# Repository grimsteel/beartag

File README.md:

# beartag

A low cost, open source BLE device tracker.

Compatible with [macless-haystack](https://github.com/dchristl/macless-haystack)

## PCB

The board is based on a WCH CH571 MCU. (Low cost BLE mcu)

It can be powered off of a single CR2032 battery, which should last at least a couple months (and potentially as long as a year)

The board includes one customizable button as well as a status LED.

## Firmware

Firmware is coming soon

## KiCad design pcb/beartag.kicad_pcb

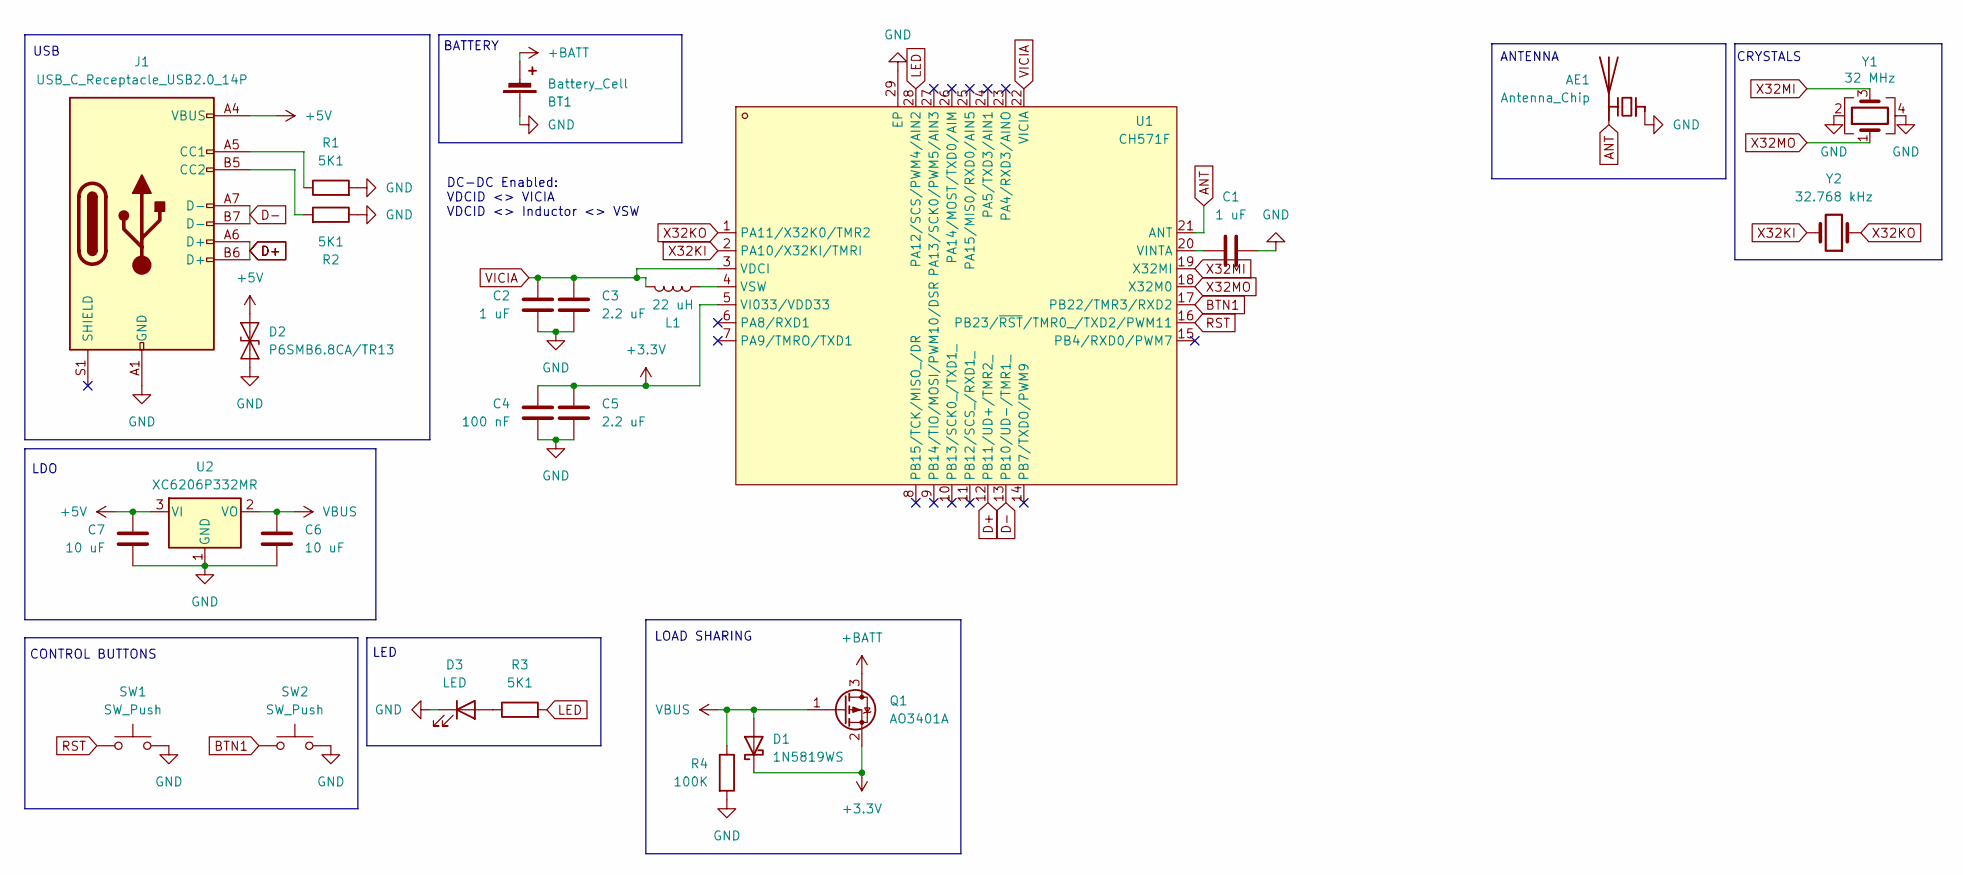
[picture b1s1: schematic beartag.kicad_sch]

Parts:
AE1: Antenna_Chip; Texas_SWRA117D_2.4GHz_Right
BT1: Battery_Cell; JST_PH_B2B-PH-K_1x02_P2.00mm_Vertical
C1, C2: 1 uF; C_0402_1005Metric; LCSC C52923
C3, C5: 2.2 uF; C_0402_1005Metric; LCSC C12530
C4: 100 nF; C_0402_1005Metric; LCSC C1525
C6, C7: 10 uF; C_0603_1608Metric; LCSC C19702
D1: 1N5819WS; D_SOD-323; LCSC C191023
D2: P6SMB6.8CA/TR13; D_SMB; LCSC C78395
D3: LED; LED_0603_1608Metric; LCSC C2286
J1: USB_C_Receptacle_USB2.0_14P; USB_C_Receptacle_HCTL_HC-TYPE-C-16P-01A; LCSC C19274016
L1: 22 uH; L_0805_2012Metric; LCSC C32375
Q1: AO3401A; SOT-23; LCSC C15127
R1, R2, R3: 5K1; R_0402_1005Metric; LCSC C25905
R4: 100K; R_0402_1005Metric; LCSC C25741
SW1, SW2: SW_Push; SW_Push_1P1T_XKB_TS-1187A; LCSC C318884
U1: CH571F; QFN-28_L4.0-W4.0-P0.40-BL-EP2.7; LCSC Part C2856288
U2: XC6206P332MR; SOT-23-3; LCSC C5446
Y1: 32 MHz; Crystal_SMD_3225-4Pin_3.2x2.5mm; LCSC C9009
Y2: 32.768 kHz; Crystal_SMD_3215-2Pin_3.2x1.5mm; LCSC C32346

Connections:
+3.3V: C4.2, C5.2, D1.1 (K), Q1.2 (S), U1.5 (VI033/VDD33)
+5V: C7.1, D2.2 (A2), J1.A4 (VBUS), J1.A9 (VBUS), J1.B4 (VBUS), J1.B9 (VBUS), U2.3 (VI)
+BATT: BT1.2 (-), Q1.3 (D)
ANT: AE1.2 (PCB_Trace), U1.21 (ANT)
BTN1: SW2.1, U1.17 (PB22/TMR3/RXD2)
D+: J1.A6 (D+), J1.B6 (D+), U1.12 (PB11/UD+/TMR2_)
D-: J1.A7 (D-), J1.B7 (D-), U1.13 (PB10/UD-/TMR1_)
GND: AE1.1 (FEED), BT1.1 (+), C1.2, C2.1, C3.1, C4.1, C5.1, C6.2, C7.2, D2.1 (A1), D3.1 (K), J1.A1 (GND), J1.A12 (GND), J1.B1 (GND), J1.B12 (GND), R1.2, R2.1, R4.2, SW1.2, SW2.2, U1.29 (EP), U2.1 (GND), Y1.2, Y1.4
LED: R3.2, U1.28 (PA12/SCS/PWM4/AIN2)
unnamed: D3.2 (A), R3.1
unnamed: J1.A5 (CC1), R1.1
unnamed: J1.B5 (CC2), R2.2
unnamed: C1.1, U1.20 (VINTA)
unnamed: L1.1, U1.4 (VSW)
RST: SW1.1, U1.16 (PB23/~RST/TMR0_/TXD2/PWM11)
VBUS: C6.1, D1.2 (A), Q1.1 (G), R4.1, U2.2 (VO)
VICIA: C2.2, C3.2, L1.2, U1.3 (VDCI), U1.22 (VICIA)
X32KI: U1.2 (PA10/X32KI/TMRI), Y2.2
X32KO: U1.1 (PA11/X32K0/TMR2), Y2.1
X32MI: U1.19 (X32MI), Y1.3
X32MO: U1.18 (X32M0), Y1.1

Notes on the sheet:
DC-DC Enabled: VDCID <> VICIA VDCID <> Inductor <> VSW
CONTROL BUTTONS
USB
LDO
LOAD SHARING
ANTENNA
LED
BATTERY
CRYSTALS

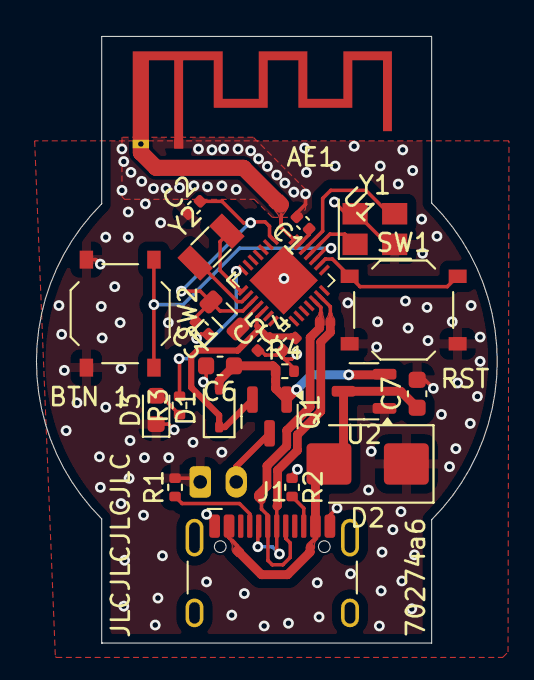
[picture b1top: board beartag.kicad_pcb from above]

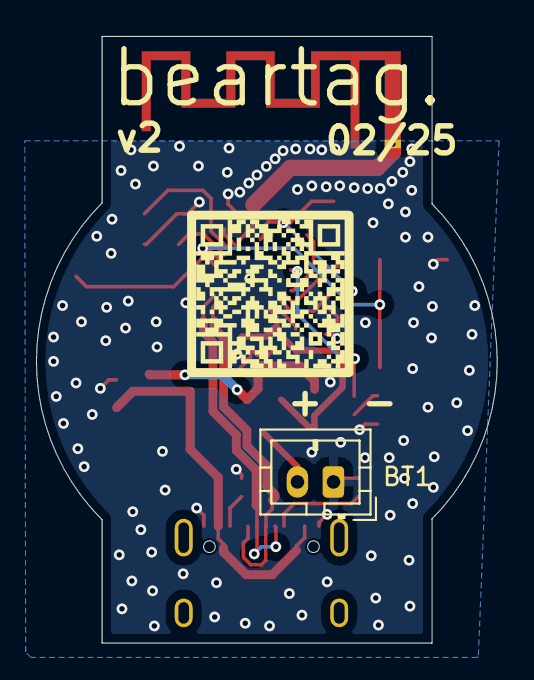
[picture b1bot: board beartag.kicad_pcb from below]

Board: 2 copper layers, 25.6 x 33.7 mm, 26 parts (2 on the bottom side), 21 nets.

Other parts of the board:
QR*****: qrcode

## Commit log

2025-05-02 pcb updates
2025-05-02 readme
2025-05-02 license
